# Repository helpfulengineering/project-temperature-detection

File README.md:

# Hardware temperature detection project

Project to build a simple, cheap, open source fever detection device. The aim is to allow symptomatic people to be quickly isolated.

On slack channel [#hardware-temperature-detection](https://app.slack.com/client/TUTSYURT3/CVCEV2V0V/thread/CV96HC6DN-1584885987.479600) from [helpfulengineering.slack.com](https://helpfulengineering.slack.com/)

Fast fever detection followed by isolation reduces the spread of infectious diseases.

## User Experience

Journey a user goes through to use the system
Initial idea is represented in the picture, taking the user from the first interface with the device to the result feedback. 
It assumes the mirror alignment but does not go into detail about it yet. 
It also lacks the user experience after the outcome communication. 

## Functional diagram

## [Project wiki](https://github.com/helpfulengineering/project-temperature-detection/wiki)

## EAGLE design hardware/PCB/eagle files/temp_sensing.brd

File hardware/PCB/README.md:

# PCB in Eagle

The current printed circuit board was designed in Eagle and imported into kicad for 3d renderings

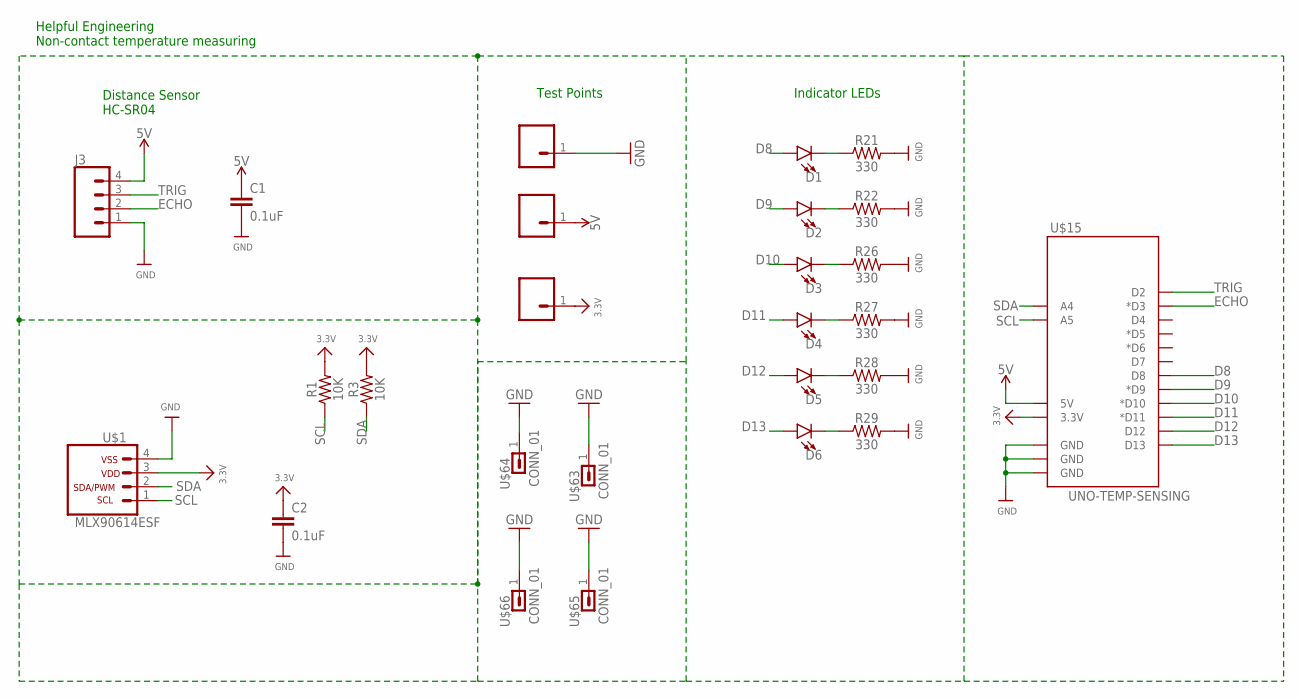
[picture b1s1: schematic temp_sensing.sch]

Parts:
C1, C2: 0.1uF; CAP-PTH-SMALL-KIT
D1, D2, D3, D4, D5, D6: LED10MM; LED_10MM
J3: CONN_04PTH; 1X04
R1, R3: 10K; AXIAL-0.3
R21, R22, R26, R27, R28, R29: 330; AXIAL-0.3
U$1: MLX90614ESF; MLX90614XCI
U$15: UNO-TEMP-SENSING; UNO_FOOTRPINT
U$20, U$31, U$59: CONN_0138MILL; 1X01-40MILL
U$63, U$64, U$65, U$66: CONN_01; 1X01-#6_MACHINE

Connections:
3.3V: C2.1, R1.P$2 (2), R3.P$2 (2), U$1.3, U$15.3.3V, U$20.1
5V: C1.1, J3.4, U$15.5V, U$59.1
D8: D1.A, U$15.D8
D9: D2.A, U$15.D9 (*D9)
D10: D3.A, U$15.D10 (*D10)
D11: D4.A, U$15.D11 (*D11)
D12: D5.A, U$15.D12
D13: D6.A, U$15.D13
ECHO: J3.2, U$15.D3 (*D3)
GND: C1.2, C2.2, J3.1, R21.P$2 (2), R22.P$2 (2), R26.P$2 (2), R27.P$2 (2), R28.P$2 (2), R29.P$2 (2), U$1.4, U$15.GND@0 (GND), U$15.GND@1 (GND), U$15.GND@2 (GND), U$31.1, U$63.1, U$64.1, U$65.1, U$66.1
unnamed: D6.C, R29.P$1 (1)
unnamed: D1.C, R21.P$1 (1)
unnamed: D2.C, R22.P$1 (1)
unnamed: D3.C, R26.P$1 (1)
unnamed: D4.C, R27.P$1 (1)
unnamed: D5.C, R28.P$1 (1)
SCL: R1.P$1 (1), U$1.1, U$15.A5
SDA: R3.P$1 (1), U$1.2, U$15.A4
TRIG: J3.3, U$15.D2

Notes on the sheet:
Test Points
Indicator LEDs
Helpful Engineering Non-contact temperature measuring
Distance Sensor HC-SR04

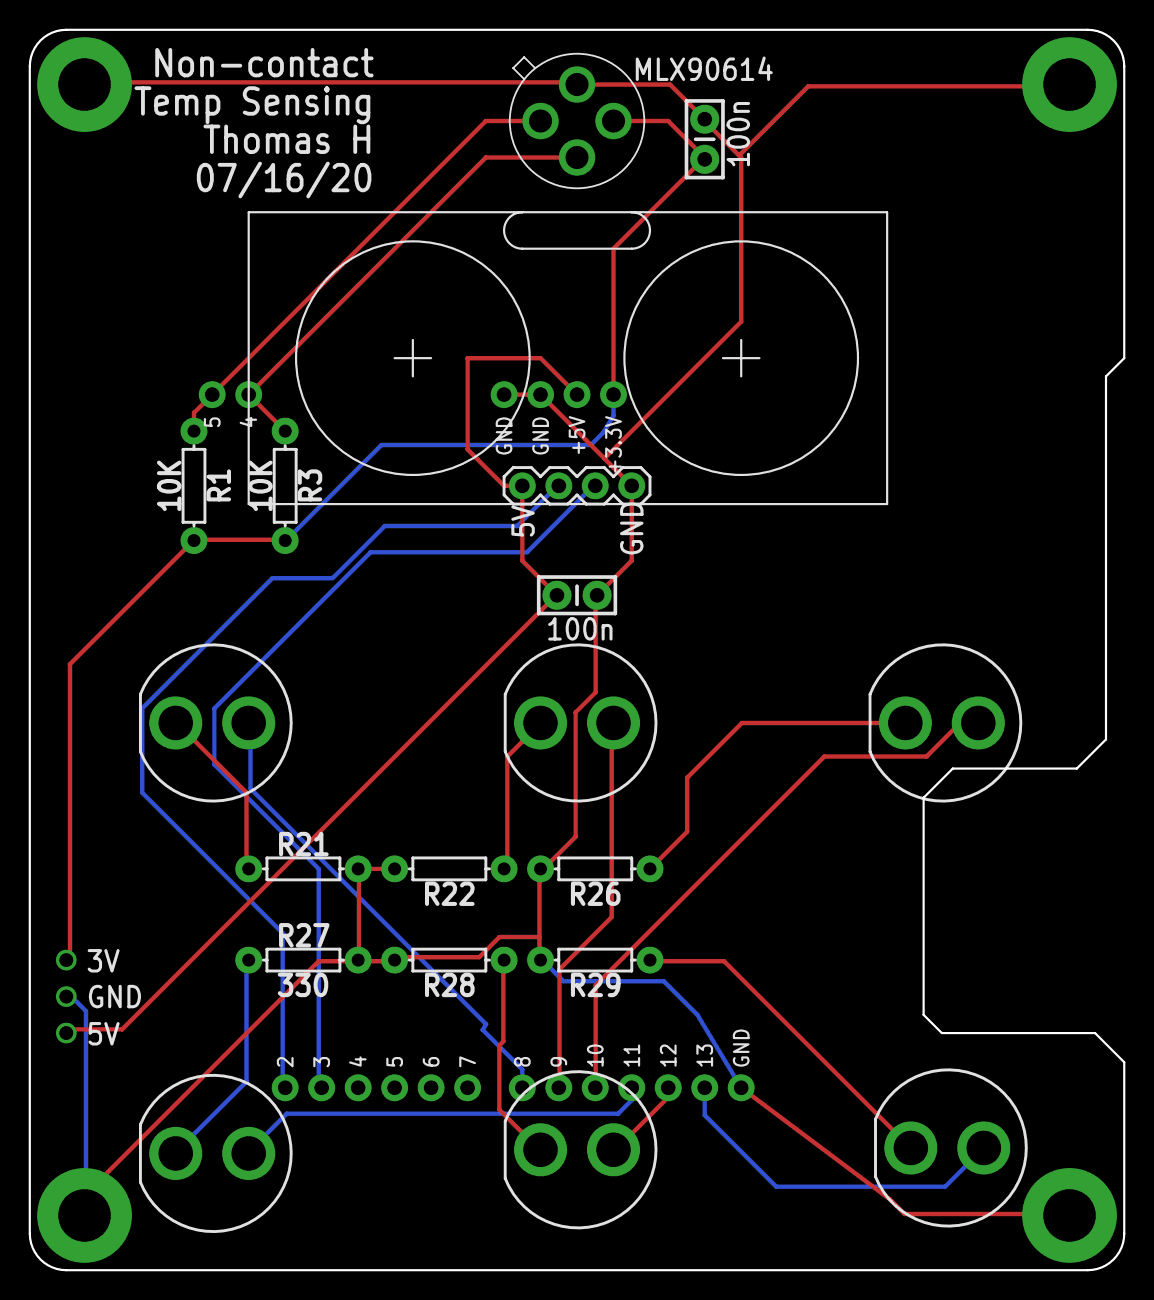
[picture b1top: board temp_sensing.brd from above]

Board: 2 copper layers, 76.2 x 86.4 mm, 26 parts (0 on the bottom side), 19 nets.

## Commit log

2020-03-24 First version
    Warning: untested
2020-03-24 Fix state logic misconceptions
2020-03-24 Remove unneeded library
2020-03-24 Reduce the delays
2020-03-25 partslist
    This is just a rough estimate. And the new design we will replace it
2020-03-25 circuit diagram
2020-03-25 Update Partslist.txt
    added circuit.io link
2020-03-25 Add PlatformIO compatibility
    Taking the assumption that the MLX90614 library to use is the Adafruit MLX90614 Library@1.0.1
2020-03-26 integrate wiki to github .md files
2020-03-26 New directory structure
2020-03-26 Move PlatformIO gitignore
2020-03-29 Minor formatting proposals
2020-03-29 Add internal link on paragraph 05
2020-03-29 Remove md files to move them to the wiki
    and add the software algorithm
2020-03-29 Remove old docs links and add wiki link
2020-04-02 Handle float instead of int for temperatures
    As we would like to be close as possible to the sensor accuracy we will handle float instead of in
2020-04-02 Add M5StickC compatibility
    Add M5StickC compatibility only with serial monitor output for the moment
2020-04-02 Code cleanup
2020-04-03 Externalize constant to a .h file
    Fever indcator pin is not used
    so remove it
2020-04-03 Add logs to make the debugging easier
2020-04-04 Code cleanup (#7)
    * Code cleanup
    * Update firmware/temperature_detection/temperature_detection.ino
    * Externalize constant to a .h file
    Fever indcator pin is not used
    so remove it
    * Add logs to make the debugging easier
2020-04-06 Create LICENSE
2020-04-06 Replace Blue Oak License by CERN-OHL-P
2020-04-06 Add average measurements
2020-04-06 Replace the 0 constraint by a more elegant ||
2020-04-06 Add UNO schematic
2020-04-06 Straighten a few wires
2020-04-07 Add missing resistors
2020-04-07 Fix the logic level of the pull resistors
2020-04-07 Update the PNG schematic
2020-04-07 Add missing resistors (#11)
    * Add missing resistors
    * Fix the logic level of the pull resistors
2020-04-14 Add intervals to function calls and user_config.h
2020-04-14 Add average measurements (#9)
    * Add average measurements
    * Replace the 0 constraint by a more elegant ||
    * Update temperature_detection.ino
    * Add intervals to function calls and user_config.h
2020-04-18 Create LICENSE (#8)
    * Create LICENSE
    * Replace Blue Oak License by CERN-OHL-P
2020-04-19 Modularize trigger function
2020-04-19 Modularize trigger function (#12)
2020-04-19 Allow a button to trigger measurements in devices without sonar
2020-04-20 Fix modular trigger logic
2020-04-20 Unify ternary operator line breaks
2020-04-21 Complete M5StickC board specific parameters
    Currently the red led of the M5StickC goes ON when we press the button, the temperature measurement is took but the red led doesn't light ON a second time to indicate fever (TO DO)
2020-04-21 Add sonar with Arduino boards on PIO
2020-04-23 Add display time, trace and change on indicators
    Add display time, if no delay the led doesn't have time to be seen
    Add default ON status for button -M5stickC button is LOW when pushed)
    Add trace for fever detected or not
    Change limit fever to 30 so as to be able to test with the skin temperature
    Change enum of fever status
    Change display status checks
2020-04-23 Fix logic
2020-04-23 Fix platform quirks
2020-04-24 Fix the negation type cast
2020-04-25 remove INVERT_BUTTON, Stab time of sensor to 0 and ENABLE SONAR macro change
    INVERT_BUTTON is finaly not necessary
    -UENABLE_SONAR don't work on my env :-1: so add -DENABLE_SONAR to other envs
    Put SENSOR_STABILIZATION_TIME to 0 with M5StickC
2020-04-25 Remove stabilization time macro and set it to 100ms
2020-04-25 Allow a button to trigger measurements in devices without sonar (#13)
    * Modularize trigger function
    * Complete M5StickC board specific parameters
    * Add traces
    * Change limit fever to 30 so as to be able to test with the skin temperature
    * Set stabilization time macro to 100ms
2020-05-24 Add support for ZTP115M
2020-05-24 Add configuration for ZTP115M
2020-05-24 Remove dead code
2020-05-24 Fix overlooked off-by-one constant
2020-05-25 Add customizable ADC steps
2020-05-26 Add LCD color display to M5StickC
    Display simple colors instead of led usage (RED/GREEN)
    RED when fever is detected after a button push
    GREEN when there is no fever after a button push
2020-05-28 Allow combined statuses
2020-05-28 Restore permanent support for LED indicators
2020-05-31 Add ENABLE conditions
    and change rectangle size to fit with M5StickC screen size
2020-06-02 invert the regression
2020-06-04 Configurable steps
2020-06-04 added code for converting voltage to temperature for ztp-115m (#15)
    * Add support for ZTP115M
    * Add configuration for ZTP115M
    * Add customizable ADC steps
2020-06-05 Add LCD color display to M5StickC (#16)
    * Add LCD color display to M5StickC
    Display simple colors instead of led usage (RED/GREEN)
    RED when fever is detected after a button push
    GREEN when there is no fever after a button push
    * Allow combined statuses
    * Restore permanent support for LED indicators
2020-06-29 Add support for additional indicators
2020-06-29 Fix PaltformIO define
2020-07-06 Add support for additional indicators (#17)
    * Add support for additional indicators
    * Fix PaltformIO define
2020-07-06 Correct logic for boards definition
    and set the serial monitor speed on platformio.ini file
    change the serial speed to 115200
2020-07-07 Correct logic for boards definition (#18)
    and set the serial monitor speed on platformio.ini file
    change the serial speed to 115200
2020-07-09 Change pins and parameters according to the prototype
2020-07-09 Change pins and parameters according to the prototype (#19)
2020-07-17 updated PCB cad files and 3d rendering
2020-07-17 added kicad files
2020-07-17 fixed images
2020-07-19 PCB files and 3d rendering (#20)
    * updated PCB cad files and 3d rendering
    * added kicad files
    * fixed images

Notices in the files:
parts and their libraries:
SparkFun-Resistors: Licensing: Creative Commons ShareAlike 4.0 International - https://creativecommons.org/licenses/by-sa/4.0
microbuilder: This work is placed in the public domain, and may be freely used for commercial and non-commercial work with the following conditions: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
